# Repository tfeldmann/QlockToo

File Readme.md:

QlockToo
========
In this repository you find the software, firmware and hardware design for the
"QlockToo", an open-source remake of the QLOCKTWO by BIEGERT & FUNK.

It is built by four Westfälische Hochschule master mechatronics students.

Software
--------
The QlockToo Software Suite is written in PySide.

Firmware
--------
We use an Arduino Micro as the central microcontroller.

License
-------
MIT-License - please refer to the License.txt in this repository.

Api
---
    @(get|set)brightness
        min                     int 0 - 255
        max                     int 0 - 255

    @(get|set)_nightmode
        brightness               int 0 - 255
        hour_start               int 0 - 23
        hour_end                 int 0 - 23
        minute_start             int 0 - 59
        minute_end               int 0 - 59

    @(get|set)kioskmode
        duration_words          int, minutes
        duration_seconds        int, minutes
        duration_temperature    int, minutes

    # matrix stream
    @m
        row     int 0 - 10
        values  bytearray

Errors
------

    !001 Unknown Command
    !002 Incorrect parameters

Authors
-------
- Thomas Feldmann
- Marlene Feldmann
- Manuel Fehmer
- Carsten Hußmann

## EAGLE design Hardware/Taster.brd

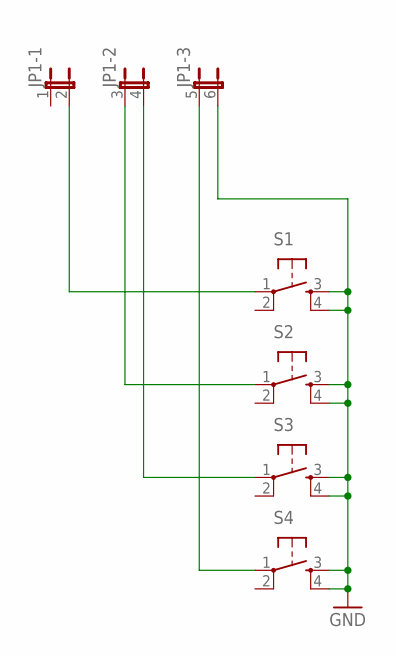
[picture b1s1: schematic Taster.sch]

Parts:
JP1: JP3QE; JP3Q
S1, S2, S3, S4: TAC_SWITCHPTH; TACTILE-PTH

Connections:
GND: JP1.6 (2), S1.3, S1.4, S2.3, S2.4, S3.3, S3.4, S4.3, S4.4
unnamed: JP1.2, S1.1
unnamed: JP1.3 (1), S2.1
unnamed: JP1.4 (2), S3.1
unnamed: JP1.5 (1), S4.1

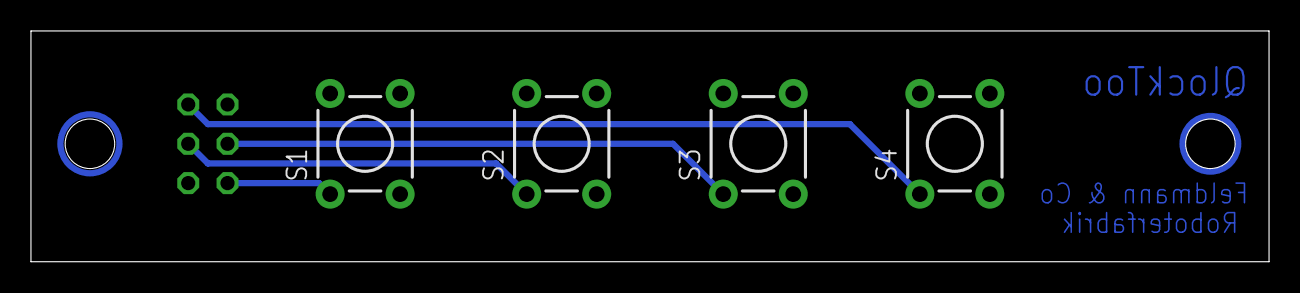
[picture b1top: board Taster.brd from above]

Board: 2 copper layers, 80.0 x 14.9 mm, 5 parts (1 on the bottom side), 5 nets.

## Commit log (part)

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2013-03-20 removed pyc files from repo
2013-03-20 added sublime project
2013-03-20 init firmware
2013-03-20 exclude project management files from project
2013-03-20 init firmware file
2013-03-21 added pattern app
2013-03-21 draw rectanlges in pattern app
2013-03-21 removed connect button in favor of a select list
2013-03-21 added todo list
2013-03-21 moved todo list to correct folder
2013-04-09 removed update button
2013-04-09 added console app
2013-04-09 better reference handling in console app
2013-04-09 updated import statements
2013-04-09 added port selection
2013-04-09 added a simulator
2013-04-09 added a device class
2013-04-09 archived todo entries
2013-04-09 added icon assets
2013-04-09 added demo app
2013-04-09 added letter layout to simulator
2013-04-09 if serial connection fails select "disconnect"
2013-04-10 rename console/pattern
2013-04-10 renamed console/pattern
2013-04-10 better imports in console __init__
2013-04-11 added marquee app
2013-04-11 show the simulator when it was hidden and now displays sth
2013-04-11 marquee app can now load font files
2013-04-11 Renamed project QlockTwo => QlockToo
2013-04-11 renamed QlockTwo => QlockToo
2013-04-11 added default font
2013-04-11 show letters while typing
2013-04-11 reformatted todo
2013-04-11 enhanced demo layout
2013-04-11 typo in font
2013-04-11 show marquee char at cursor position
2013-04-11 new marquee layout
2013-04-12 new font dimensions
2013-04-12 enhanced font alignment
2013-04-12 added small letters and german umlaute
2013-04-12 marquee now works
2013-04-12 added corners to simulator
2013-04-12 fixed alignment of small i
2013-04-12 setting the speed in marquee
2013-04-12 documentation
2013-04-12 deactivated tracking
2013-04-12 set corners in demos
2013-04-14 added : and ; to font
2013-04-14 added +*/
2013-04-14 updated todo
2013-04-14 added =
2013-04-14 added device display properties
2013-04-14 added myself as second author
2013-04-14 refactoring
2013-04-15 added combined asset file
2013-04-15 added test code on isolated app start
2013-04-15 moved default font into a py file
2013-04-15 added snake app
2013-04-15 close windows on closing
2013-04-15 snake game is playable
2013-04-16 added score and reset options
2013-04-16 removed pause functionality
2013-04-16 bugfixes and documentation
2013-04-17 refactoring the marquee into its own marquee class
2013-04-22 Added LedBar Testcode
2013-04-23 wave demo now moves in circles
2013-04-23 added helix demo
2013-04-24 laid out general structure to firmware
2013-04-24 renamed scmd_ functions to api_
2013-04-24 separated matrix update / init
2013-04-24 formatting
2013-04-24 added comments to snake model
2013-04-24 new todo ideas
2013-04-26 api string formatting
2013-04-26 renamed Matrix.ino to Display.ino
2013-04-26 serial communication now works
2013-04-26 new helix code
2013-04-26 renamed shutdown -> close
2013-04-26 tried to add multiplexing
2013-05-09 faster serial connection
2013-05-09 added time module
2013-05-09 nicer letter layout coding
2013-05-09 fixed pong game
2013-05-09 cleaned up dcf77 code
2013-05-09 removed serial calls in interrupts
2013-05-09 removed timer from display module
2013-05-09 clearer error messages
2013-05-13 added settings panel
2013-07-05 Added License
2013-07-05 removed license from font and added a docstring.
2013-07-05 added buildtools
    This means all _ui.py files are generated by the setup and buildtools
    scripts on the fly.
2013-07-05 file renames and exclusions
2013-07-05 added frontplate
2013-07-05 added qlocktoo schematics
2013-07-05 added button board schematics
2013-07-05 added screenshot
2013-07-05 overhauled design
2013-07-05 added firmware settings
2013-07-05 buildtools now converts qt resource files
2013-07-05 buildtools enhancements
2013-07-06 Updated Screenshot
2013-07-08 new method startApp
2013-07-08 added timewords app as default view
2013-07-08 fixes a bug where the snake app wouldn't be terminated correctly
2013-07-08 removed buildtools call in setup.py
2013-07-09 added corner case
2013-07-09 added connect layout
2013-07-13 added "<"
2013-07-15 corrected NEUN (was HNEUN)
2013-08-15 major project restructuring
2013-08-15 cleanup for software v1.0
2013-08-15 updated software readme
2013-08-23 pep8 formatting
2013-08-23 added init.py to qlocktoo dir
2013-10-09 added lowpass to helix
2013-10-14 added libraries
2013-10-14 enhanced lowpass
2013-10-14 commented unfinished api commands
2013-10-14 added timer
2013-10-14 added display initialization
2013-10-14 dump time in main loop, not in interrupt
2013-10-14 variable renaming
2013-10-14 added api for switching states
2013-10-14 added a statemachine
2013-10-14 integrated time_is_updated flag
2013-10-14 added matrix numbers
2013-10-16 added Matrix code
2013-10-16 added illustrator frontplate file
2013-10-16 variable types
2013-10-16 fixed bug in array mask handling
2013-10-16 moved matrix and corner variables into globals file
2013-10-16 matrix is only uint8_t
2013-10-16 added function prototype for matrix_timewords
2013-10-16 added matrix display to controller
2013-10-18 added frontplate with throughhole
2013-10-21 added Game of Life and Matrix Demo
2013-10-26 added a command to manually show the next row
2013-10-26 removed file leddriver
2013-10-26 added alternative I2C library
2013-10-28 cleanup
2013-10-28 added Button tab
2013-10-28 fixed some bugs with timewords
2013-10-28 small modifications
2013-10-28 disable debug output
2013-10-28 refactoring for display_update
2013-10-28 added seconds
2013-10-28 added thermo file
2013-10-28 added @celsius command
2013-10-28 simplified matrix syntax
2013-10-28 added bounce library
2013-10-28 added button file
2013-10-28 reformating and button handling
2013-10-28 comment formatting
2013-10-28 upped version number
2013-10-28 formatting and changelog
2013-10-28 added global brightness setting
2013-10-28 added a filter for the brightness values
2013-10-28 increased the press duration to change to seconds view to 1,5 s
2013-10-28 removed unneccessary comment
2013-10-28 formatting modifications to brightness filter
2013-10-29 Bounce formatting
2013-10-29 filter adjustment
2013-11-06 added matrix streaming api
2013-11-06 added brightness modes
2013-11-06 added digitalWriteFast Library
2013-11-06 added streaming
2013-11-06 now using a LUT instead of map function
2013-11-06 moved button updated to loop, state machine updates to display
2013-11-15 added documentation
2013-11-15 added thermo_celsius
2013-11-15 simplified brightness filter
2013-11-15 connected the dcf77 to a different pin
2013-11-15 wieder gelöscht
2013-11-15 added software and firmware chapter
2013-11-15 using range in favor of xrange
2013-11-15 enhanced comment
2013-11-20 add Elektronik
2013-11-20 no message
2013-11-20 Einleitung
2013-11-20 Zweispaltig
2013-11-20 Inhalt und Platzhalter für Grafiken
2013-11-20 Elektronik
2013-11-20 Demotexte
2013-11-20 bauteilbeschreibung
2013-11-20 Schrift etwas verkleinert
2013-11-20 disable serial connection for now
2013-11-20 Screenshot -> Manager
2013-11-20 added Screenshots
2013-11-20 Einleitung I
2013-11-20 multicol hinzugefügt
2013-11-20 multiline in Software
2013-11-20 Arduino pic
2013-11-20 minipage figure
2013-11-20 Einleitung II - eine Spalte
2013-11-20 wandbild
2013-11-20 Einleitung 2 Spalten
2013-11-20 added connect dialog
2013-11-20 added ground plate drawing
2013-11-20 Einleitung : Formulierung / Fehler
2013-12-04 bugfix no longer needed
2013-12-04 init
2013-12-04 error
2013-12-04 better device management
2013-12-04 new icons
2013-12-04 font
2013-12-04 added device connection
2013-12-04 demo with fps and added assets
2013-12-04 added compiles assets, because windows pcs often don't install the command line tools
2013-12-04 added converted ui files in vc
2013-12-04 Korrektur - nach Möglichkeit vermeiden der Umgangssprache
2013-12-04 corrected icon
2013-12-04 show message if not connected
2013-12-04 bugs
2013-12-04 Kapitelstart Konstruktion
2013-12-04 Verbesserung
2013-12-04 zu viele Leerzeichen
2013-12-04 brightness
2013-12-11 eagle
2013-12-11 Unterkapitel - zu Unterschriften
    Korrekturen / Konstruktion
2013-12-11 Konstruktion erweitert - Abbildungen usw.
2013-12-11 fixed some bugs in display code
2013-12-11 added my email adress
2013-12-11 deleted button page
2013-12-11 better variable declaration
2013-12-11 simplified brightness
2013-12-11 added some pictures
2013-12-11 deleted brightness api
2013-12-11 added buttons to controller
2013-12-11 added some commands
2013-12-11 update brightness explicitely in state
2013-12-11 start in brightest mode
2013-12-11 refactored into font.h
2013-12-11 Change numbers
2013-12-11 Es lacht ne Kuh
2013-12-12 added new state
2013-12-13 Bilder und Konstruktion
2013-12-13 Bilder Bilder Bilder
2013-12-13 added @settime
2013-12-13 fast connection
2013-12-13 disconnect on close
2013-12-13 print clock protocol data
2013-12-16 Konstruktion und Produktion -.-
2013-12-16 Korrekturen und Umbenennung Unterkapitel
2013-12-16 added timewords
2013-12-16 pong is now pixeltest
2013-12-16 a bit of refactoring
2013-12-16 seconds
2013-12-16 Korrekturen - Literaturverzeichnis hinzugefügt
2013-12-16 Korrektur - Bilder - usw.
2013-12-16 removed .rej file
2013-12-16 ClockToo -> QlockToo
2013-12-16 verbessert
2013-12-16 added eventloop
2013-12-16 Firmware / Software Doku
2013-12-16 Kapitel Funkionen - zur Erklärung der Taster :)
2013-12-16 Kapitel Funktionen
2013-12-16 Firmware Kapitel
2013-12-16 Funktionen
2013-12-18 Laufschrift hinzugefügt plus Fehlerkorrektur
2013-12-18 elektronik: platinenlayout
2013-12-18 Formulierung
2013-12-18 Wünsche LENI, Software - Bilder
2013-12-18 Formulierung, Bilder
2013-12-18 Änderung der Struktur - möglichst einfach - zu viele Unterkapitel "ohne" Inhalt gefallen mir nicht
2013-12-18 struktur
2013-12-18 Anschluss
2013-12-18 Firmware - Struktur
2013-12-18 Elektronik fertig?!
2013-12-18 Wünsche TODO
2013-12-18 Minimale Korrekturen
2013-12-19 Wer spielt denn hier an der Firmware rum!
2013-12-19 Firmware now uses the Bounce library instead of the selfmade debouncer
2013-12-19 added state switch to dcf77
2013-12-19 display driver enhancements
2013-12-19 Bounce library modifications
2013-12-19 Added new state WAIT_FOR_DCF
2013-12-19 use of interrupts(); and noInterrupts()
2013-12-19 better formatting for display driver
2013-12-19 commented on thermo values
2013-12-19 bugfix for time_dump
2013-12-19 modified serialcommand parameters
2013-12-20 thermo changes
2013-12-20 just the first three buttons for waiting state
2013-12-20 FUNK
2013-12-20 added demo states
2013-12-20 interrupt handling
2013-12-20 added white state
2013-12-20 timer bugfix!
2013-12-20 buttons
2013-12-20 added rudimentary matrix prototype
2013-12-20 matrix fixes
2013-12-20 added random seed to matrix demo
2013-12-25 snake enhancements
2014-01-02 minor firmware modifications
2014-01-02 Kapitel Firmware
2014-01-06 Stromverbrauch
2014-01-06 Platinenlayout
2014-01-06 Formatierung
2014-01-06 Formatierung der Einleitung
2014-01-06 Funktionen Kapitel
2014-01-06 Foto Platine_bestueckt
2014-01-06 foto ersetzt
2014-01-06 Software und Firmware
2014-01-06 Software Start - Thomas übernimmt
2014-01-06 Bildunterschrift entfernt
2014-01-06 Software Bilder
2014-01-06 Formatierung und Grafiken
2014-01-06 Reihenfolge - Überschrift
2014-01-06 qlock -> clock
2014-01-06 Überschriften
2014-01-06 Englischer Titel
2014-01-06 Bild
2014-01-06 Konstruktion und Elektronik getauscht
2014-01-06 Titel
2014-01-06 Demonstrationen
2014-01-06 Caption
2014-01-06 schaltplan?!
2014-01-06 Funktionen mit in das Firmware Kapitel gepackt
2014-01-06 Elektronik Seitenlayout
2014-01-06 Überschrift aus dem Inhaltsverzeichnis genommen
2014-01-06 Sekunden und Temperatur
2014-01-06 mirco
2014-01-10 removed eventloop and snake background
2014-03-22 separated device and simulator
2014-03-22 Brightness controls
2014-03-22 added console output
2014-03-22 bugfix init simulator
2014-03-26 added configuration
2014-03-30 added bresenham line algorithm
2015-06-09 added small fade effect everywhere
2015-06-09 sanity check for dcf parser
2015-06-09 updated application to support python3
2015-06-09 python3 support
2017-08-01 big code cleanup. Remove configuration, kioskmode, nightmode. Refactor modes into their own files
2017-09-12 add new wave demo

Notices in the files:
parts and their libraries:
SparkFun: Licensing: CC v3.0 Share-Alike You are welcome to use this library for commercial purposes.
